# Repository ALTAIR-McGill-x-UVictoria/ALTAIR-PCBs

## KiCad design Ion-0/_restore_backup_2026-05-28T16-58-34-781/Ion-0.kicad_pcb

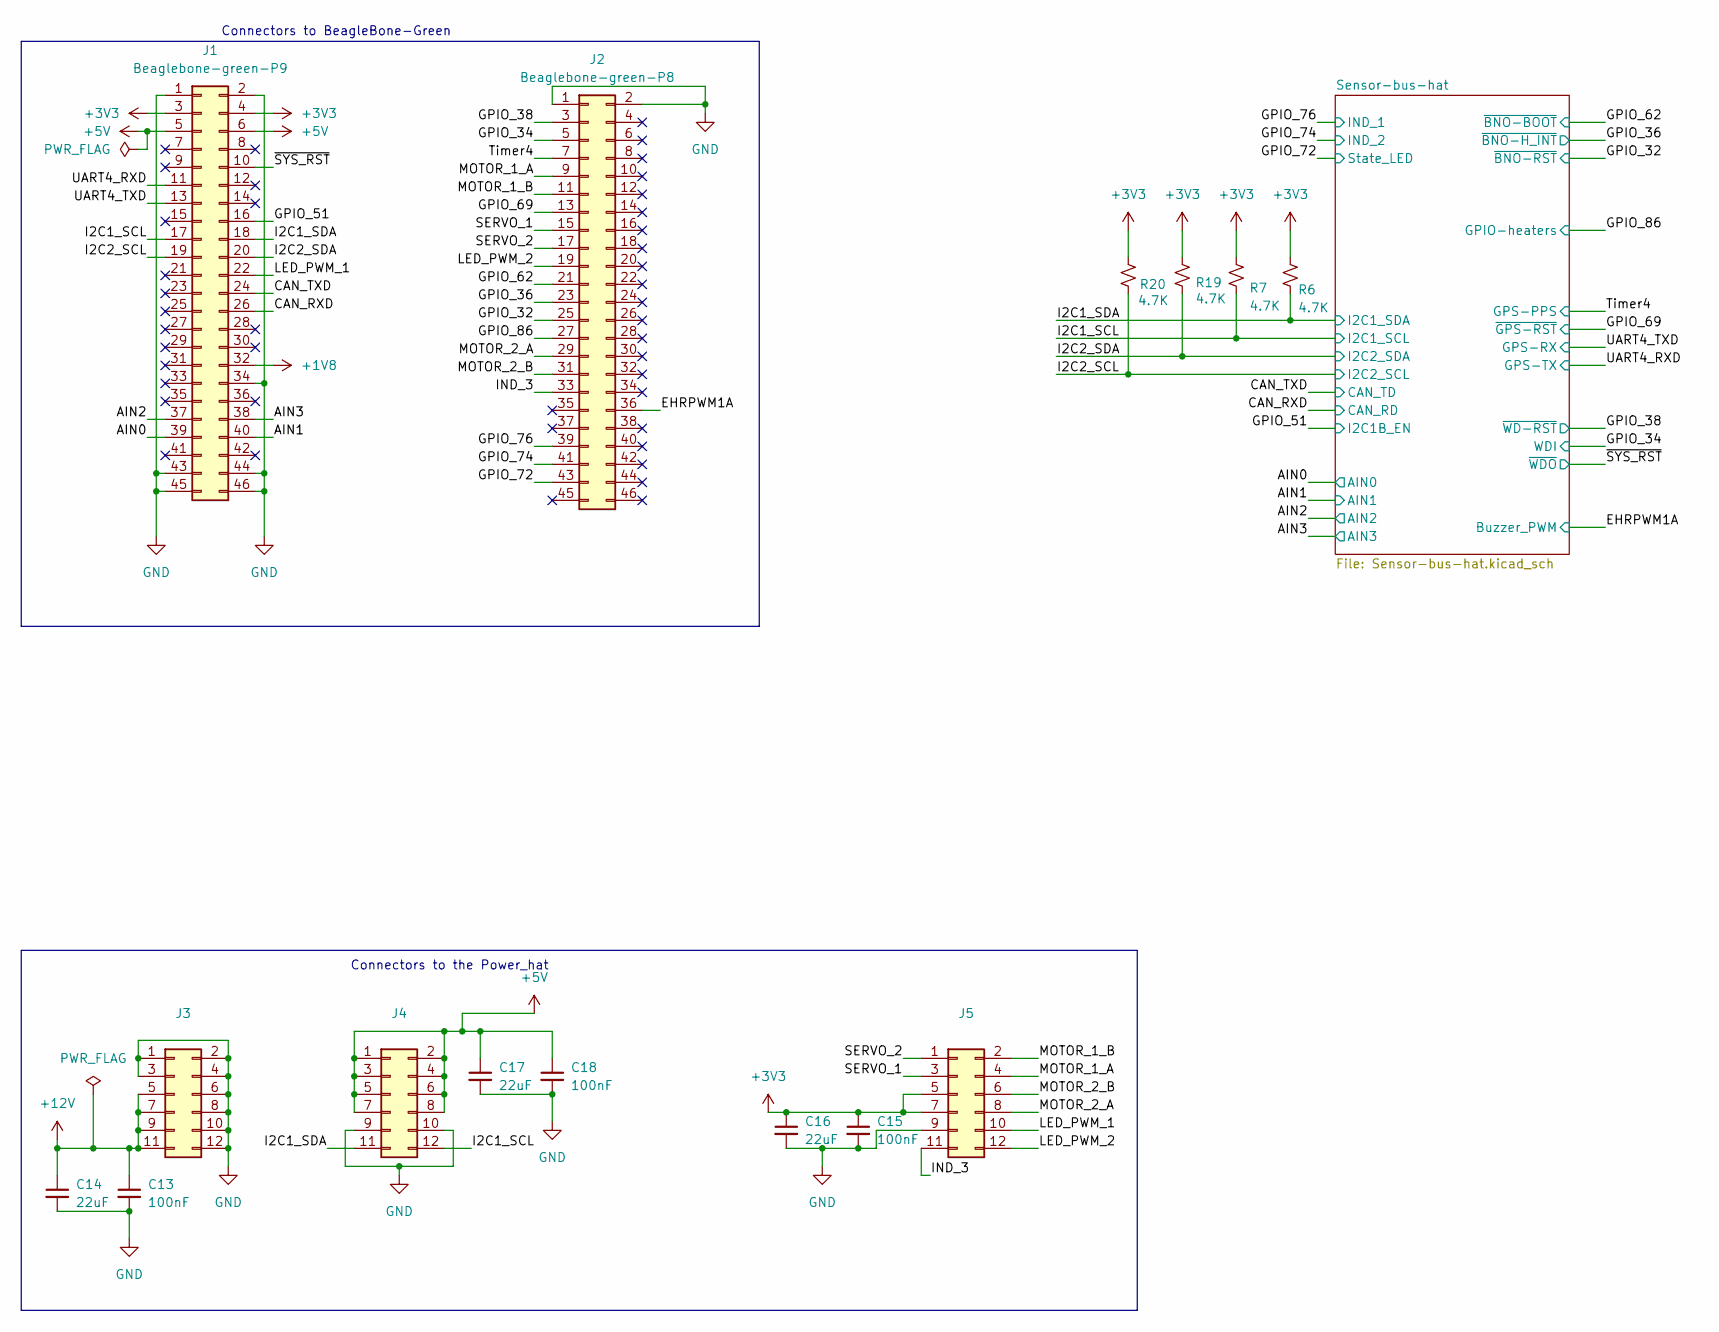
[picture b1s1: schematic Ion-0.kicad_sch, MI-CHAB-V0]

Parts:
C13, C15, C18: 100nF; C_0603_1608Metric
C14, C16, C17: 22uF; C_0603_1608Metric
J1: Beaglebone-green-P9; PinHeader_2x23_P2.54mm_Vertical
J2: Beaglebone-green-P8; PinHeader_2x23_P2.54mm_Vertical
J3, J4, J5: Conn_02x06_Odd_Even; PinSocket_2x06_P2.54mm_Vertical
R6, R7, R19, R20: 4.7K; R_0603_1608Metric_Pad0.98x0.95mm_HandSolder

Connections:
+1V8: J1.32; also elsewhere on the board
+3V3: C15.1, C16.1, J1.3, J1.4, J5.5, J5.7, R6.2, R7.1, R19.1, R20.1; also elsewhere on the board
+5V: C17.1, C18.1, J1.5, J1.6, J4.1, J4.2, J4.3, J4.4, J4.5, J4.6, J4.7, J4.8; also elsewhere on the board
+12V: C13.1, C14.1, J3.5, J3.7, J3.9, J3.11
/AIN0: J1.39; also elsewhere on the board
/AIN1: J1.40; also elsewhere on the board
/AIN2: J1.37; also elsewhere on the board
/AIN3: J1.38; also elsewhere on the board
/CAN_RXD: J1.26; also elsewhere on the board
/CAN_TXD: J1.24; also elsewhere on the board
/EHRPWM1A: J2.36; also elsewhere on the board
/GPIO_32: J2.25; also elsewhere on the board
/GPIO_34: J2.5; also elsewhere on the board
/GPIO_36: J2.23; also elsewhere on the board
/GPIO_38: J2.3; also elsewhere on the board
/GPIO_51: J1.16; also elsewhere on the board
/GPIO_62: J2.21; also elsewhere on the board
/GPIO_69: J2.13; also elsewhere on the board
/GPIO_72: J2.43; also elsewhere on the board
/GPIO_74: J2.41; also elsewhere on the board
/GPIO_76: J2.39; also elsewhere on the board
/GPIO_86: J2.27; also elsewhere on the board
/I2C1_SCL: J1.17, J4.12, R7.2; also elsewhere on the board
/I2C1_SDA: J1.18, J4.11, R6.1; also elsewhere on the board
/I2C2_SCL: J1.19, R20.2; also elsewhere on the board
/I2C2_SDA: J1.20, R19.2; also elsewhere on the board
/IND_3: J2.33, J5.11
/LED_PWM_1: J1.22, J5.10
/LED_PWM_2: J2.19, J5.12
/MOTOR_1_A: J2.9, J5.4
/MOTOR_1_B: J2.11, J5.2
/MOTOR_2_A: J2.29, J5.8
/MOTOR_2_B: J2.31, J5.6
/SERVO_1: J2.15, J5.3
/SERVO_2: J2.17, J5.1
/Timer4: J2.7; also elsewhere on the board
/UART4_RXD: J1.11; also elsewhere on the board
/UART4_TXD: J1.13; also elsewhere on the board
/~SYS_RST: J1.10; also elsewhere on the board
GND: C13.2, C14.2, C15.2, C16.2, C17.2, C18.2, J1.1, J1.2, J1.34, J1.43, J1.44, J1.45, J1.46, J2.1, J2.2, J3.1, J3.2, J3.3, J3.4, J3.6, J3.8, J3.10, J3.12, J4.9, J4.10, J5.9; also elsewhere on the board

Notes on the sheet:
Connectors to BeagleBone-Green
Connectors to the Power_hat

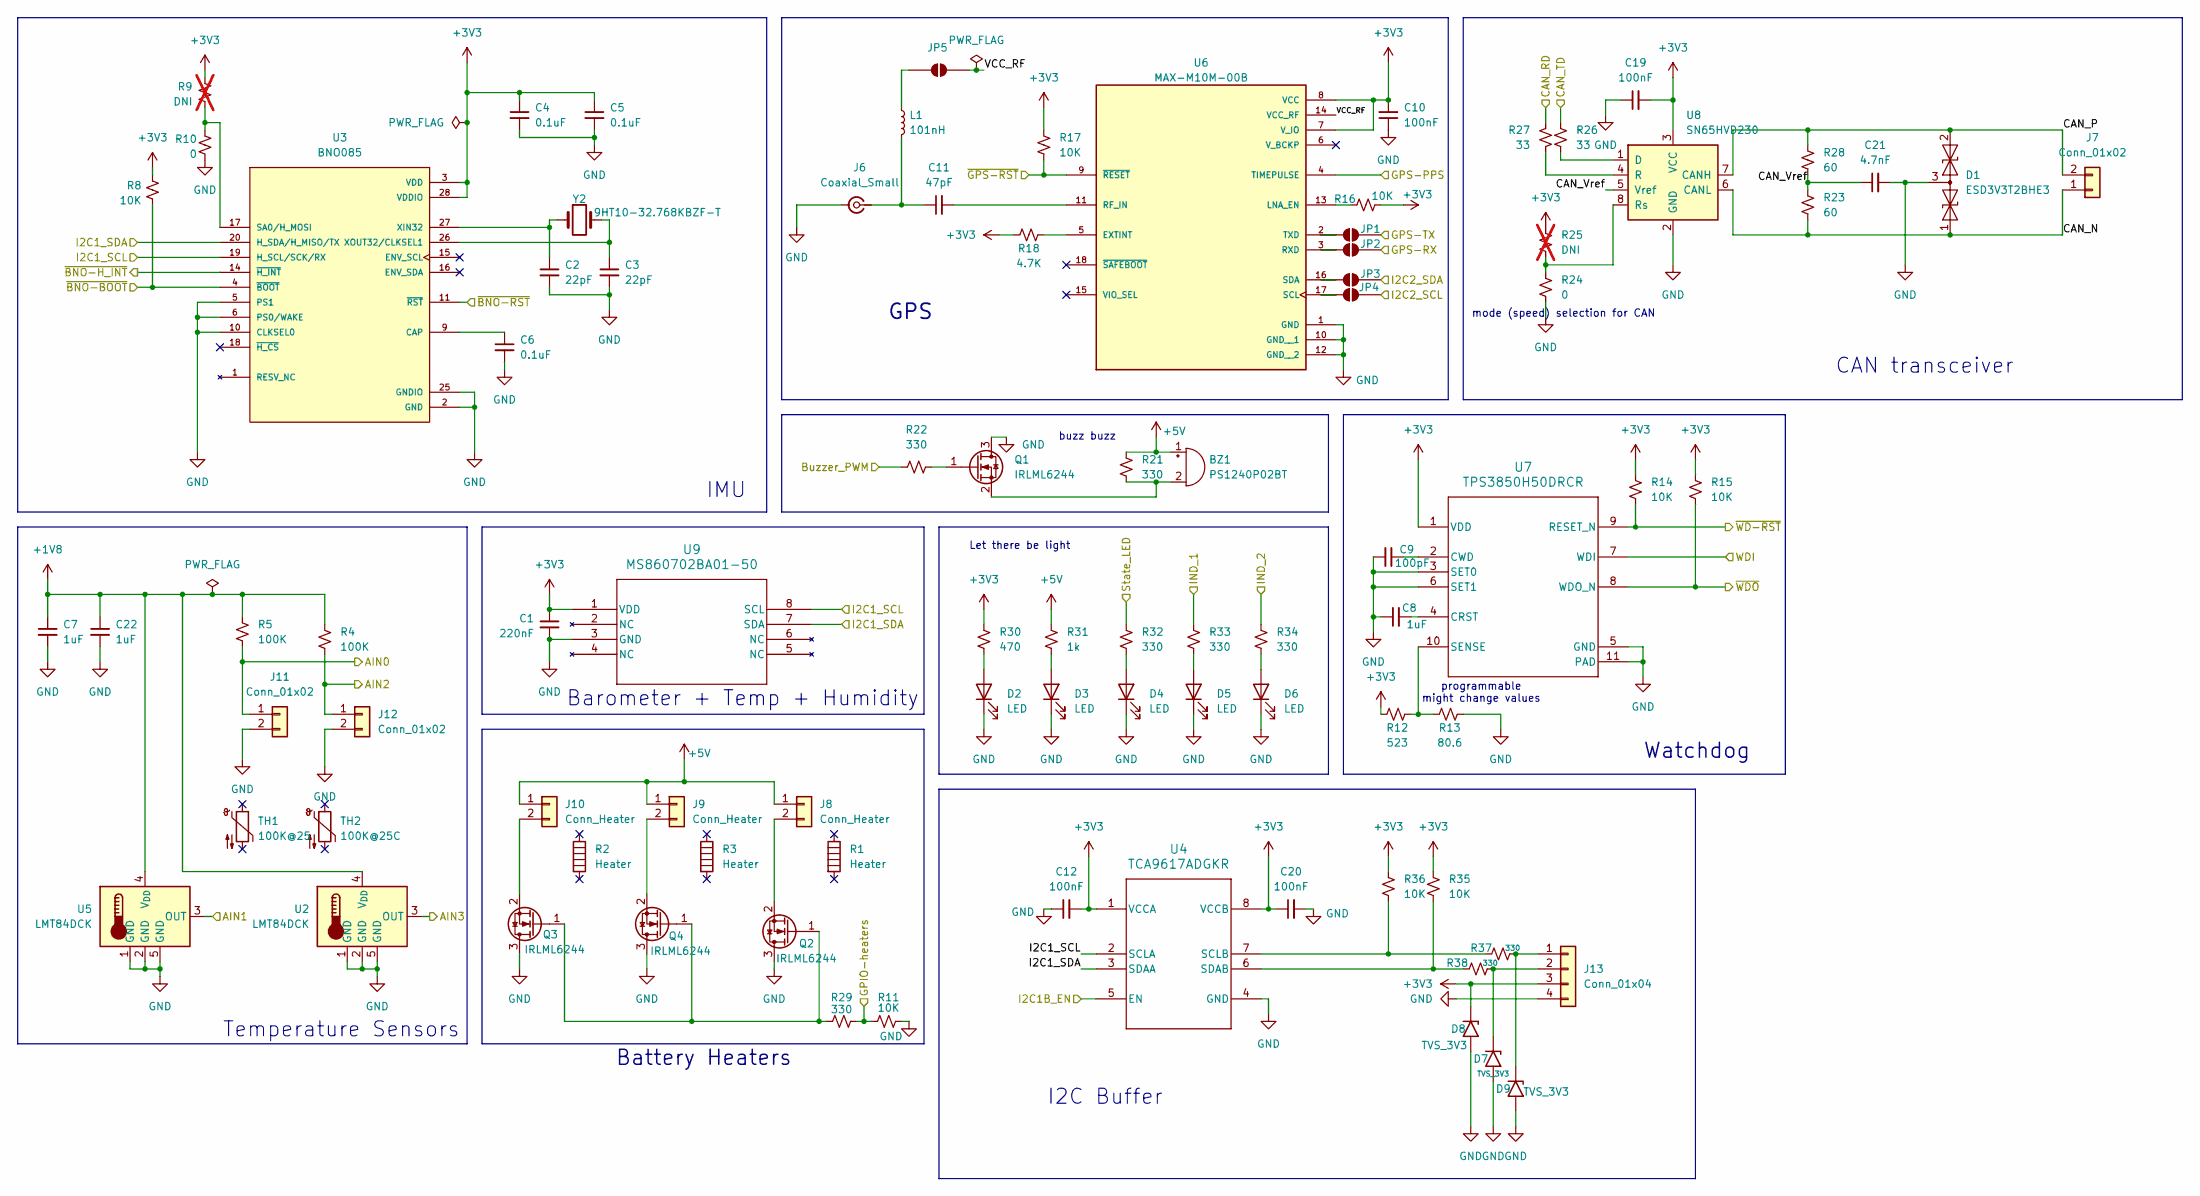
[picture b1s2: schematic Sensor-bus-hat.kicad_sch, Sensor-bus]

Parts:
BZ1: PS1240P02BT; Buzzer_TDK_PS1240P02BT_D12.2mm_H6.5mm
C1: 220nF; C_0603_1608Metric
C2, C3: 22pF; C_0603_1608Metric
C4, C5, C6: 0.1uF; C_0603_1608Metric
C7, C8, C22: 1uF; C_0603_1608Metric
C9: 100pF; C_0603_1608Metric
C10, C12, C19, C20: 100nF; C_0603_1608Metric
C11: 47pF; C_0603_1608Metric
C21: 4.7nF; C_0603_1608Metric
D1: ESD3V3T2BHE3; SOT-23
D2, D3, D4, D5, D6: LED; LED_0805_2012Metric
D7, D8, D9: TVS_3V3; D_0402_1005Metric_Pad0.77x0.64mm_HandSolder
J6: Coaxial_Small; SMA_Samtec_SMA-J-P-H-ST-EM1_EdgeMount
J7, J11, J12: Conn_01x02; JST_SH_SM02B-SRSS-TB_1x02-1MP_P1.00mm_Horizontal
J8, J9, J10: Conn_Heater; JST_SH_SM02B-SRSS-TB_1x02-1MP_P1.00mm_Horizontal
J13: Conn_01x04; JST_SH_SM04B-SRSS-TB_1x04-1MP_P1.00mm_Horizontal
JP1, JP2, JP3, JP4, JP5: SolderJumper_2_Open; SolderJumper-2_P1.3mm_Open_TrianglePad1.0x1.5mm
L1: 101nH; L_0402_1005Metric
Q1, Q2, Q3, Q4: IRLML6244; SOT-23
R1, R2, R3: Heater
R4, R5: 100K; R_0603_1608Metric_Pad0.98x0.95mm_HandSolder
R8, R11, R14, R15, R16, R17, R35, R36: 10K; R_0603_1608Metric_Pad0.98x0.95mm_HandSolder
R9, R25: DNI; R_0603_1608Metric_Pad0.98x0.95mm_HandSolder; not fitted
R10, R24: 0; R_0603_1608Metric_Pad0.98x0.95mm_HandSolder
R12: 523; R_0603_1608Metric_Pad0.98x0.95mm_HandSolder
R13: 80.6; R_0603_1608Metric_Pad0.98x0.95mm_HandSolder
R18: 4.7K; R_0603_1608Metric_Pad0.98x0.95mm_HandSolder
R21, R22, R29, R32, R33, R34, R37, R38: 330; R_0603_1608Metric_Pad0.98x0.95mm_HandSolder
R23, R28: 60; R_0603_1608Metric_Pad0.98x0.95mm_HandSolder
R26, R27: 33; R_0603_1608Metric_Pad0.98x0.95mm_HandSolder
R30: 470; R_0603_1608Metric_Pad0.98x0.95mm_HandSolder
R31: 1k; R_0603_1608Metric_Pad0.98x0.95mm_HandSolder
TH1: 100K@25
TH2: 100K@25C
U2, U5: LMT84DCK; SOT-353_SC-70-5
U3: BNO085; IC_BNO085; PARTREV v1.17
U4: TCA9617ADGKR; TCA9617A
U6: MAX-M10M-00B; XCVR_MAX-M10M-00B; PARTREV C1
U7: TPS3850H50DRCR; TPS3850
U8: SN65HVD230; SOIC-8_3.9x4.9mm_P1.27mm
U9: MS860702BA01-50; MS860702BA01-50_TEC
Y2: 9HT10-32.768KBZF-T; L_1206_3216Metric

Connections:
+1V8: C7.1, C22.1, R4.1, R5.1, U2.4 (V_{DD}), U5.4 (V_{DD}); also elsewhere on the board
+3V3: C1.1, C4.1, C5.1, C10.2, C12.2, C19.2, C20.1, D8.1 (A1), J13.3, R8.1, R9.1, R12.1, R14.1, R15.1, R16.2, R17.1, R18.2, R25.1, R30.1, R35.1, R36.1, U3.3 (VDD), U3.28 (VDDIO), U4.1 (VCCA), U4.8 (VCCB), U6.7 (V_IO), U6.8 (VCC), U7.1 (VDD), U8.3 (VCC), U9.1 (VDD); also elsewhere on the board
+5V: BZ1.1 (+), J8.1, J9.1, J10.1, R21.1, R31.1; also elsewhere on the board
/AIN0: J11.1, R5.2; also elsewhere on the board
/AIN1: U5.3 (OUT); also elsewhere on the board
/AIN2: J12.1, R4.2; also elsewhere on the board
/AIN3: U2.3 (OUT); also elsewhere on the board
/CAN_RXD: R27.1; also elsewhere on the board
/CAN_TXD: R26.1; also elsewhere on the board
/EHRPWM1A: R22.1; also elsewhere on the board
/GPIO_32: U3.11 (~RST); also elsewhere on the board
/GPIO_34: U7.7 (WDI); also elsewhere on the board
/GPIO_36: U3.14 (~H_INT); also elsewhere on the board
/GPIO_38: R14.2, U7.9 (RESET_N); also elsewhere on the board
/GPIO_51: U4.5 (EN); also elsewhere on the board
/GPIO_62: R8.2, U3.4 (~BOOT); also elsewhere on the board
/GPIO_69: R17.2, U6.9 (~RESET); also elsewhere on the board
/GPIO_72: R32.1; also elsewhere on the board
/GPIO_74: R34.1; also elsewhere on the board
/GPIO_76: R33.1; also elsewhere on the board
/GPIO_86: R11.1, R29.1; also elsewhere on the board
/I2C1_SCL: U3.19 (H_SCL/SCK/RX), U4.2 (SCLA), U9.8 (SCL); also elsewhere on the board
/I2C1_SDA: U3.20 (H_SDA/H_MISO/TX), U4.3 (SDAA), U9.7 (SDA); also elsewhere on the board
/I2C2_SCL: JP4.2 (B); also elsewhere on the board
/I2C2_SDA: JP3.2 (B); also elsewhere on the board
/Sensor-bus-hat/CAN_Vref: C21.1, R23.1, R28.2, U8.5 (Vref)
/Sensor-bus-hat/VCC_RF: JP5.2 (B), U6.14 (VCC_RF)
/Timer4: U6.4 (TIMEPULSE); also elsewhere on the board
/UART4_RXD: JP1.2 (B); also elsewhere on the board
/UART4_TXD: JP2.2 (B); also elsewhere on the board
/~SYS_RST: R15.2, U7.8 (WDO_N); also elsewhere on the board
GND: C1.2, C2.2, C3.2, C4.2, C5.2, C6.2, C7.2, C8.1, C9.2, C10.1, C12.1, C19.1, C20.2, C21.2, C22.2, D1.3 (common), D2.1 (K), D3.1 (K), D4.1 (K), D5.1 (K), D6.1 (K), D7.2 (A2), D8.2 (A2), D9.2 (A2), J6.2 (Ext), J11.2, J12.2, J13.4, Q1.3 (D), Q2.3 (D), Q3.3 (D), Q4.3 (D), R10.2, R11.2, R13.1, R24.2, U2.1 (GND), U2.2 (GND), U2.5 (GND), U3.2 (GND), U3.5 (PS1), U3.6 (PS0/WAKE), U3.10 (CLKSEL0), U3.25 (GNDIO), U4.4 (GND), U5.1 (GND), U5.2 (GND), U5.5 (GND), U6.1 (GND), U6.10 (GND__1), U6.12 (GND__2), U7.3 (SET0), U7.5 (GND), U7.6 (SET1), U7.11 (PAD), U8.2 (GND), U9.3 (GND); also elsewhere on the board
unnamed: BZ1.2 (-), Q1.2 (S), R21.2
unnamed: D2.2 (A), R30.2
unnamed: D3.2 (A), R31.2
unnamed: D4.2 (A), R32.2
unnamed: D5.2 (A), R33.2
unnamed: D6.2 (A), R34.2
unnamed: D7.1 (A1), J13.2, R38.2
unnamed: D9.1 (A1), J13.1, R37.2
unnamed: C11.1, J6.1 (In), L1.2
unnamed: J8.2, Q2.2 (S)
unnamed: J9.2, Q4.2 (S)
unnamed: J10.2, Q3.2 (S)
unnamed: JP1.1 (A), U6.2 (TXD)
unnamed: JP2.1 (A), U6.3 (RXD)
unnamed: JP3.1 (A), U6.16 (SDA)
unnamed: JP4.1 (A), U6.17 (SCL)
unnamed: JP5.1 (A), L1.1
unnamed: Q1.1 (G), R22.2
unnamed: Q2.1 (G), Q3.1 (G), Q4.1 (G), R29.2
unnamed: C6.1, U3.9 (CAP)
unnamed: R9.2, R10.1, U3.17 (SA0/H_MOSI)
unnamed: C2.1, U3.27 (XIN32), Y2.1
unnamed: C3.1, U3.26 (XOUT32/CLKSEL1), Y2.2
unnamed: R36.2, R37.1, U4.7 (SCLB)
unnamed: R35.2, R38.1, U4.6 (SDAB)
unnamed: R18.1, U6.5 (EXTINT)
unnamed: R16.1, U6.13 (LNA_EN)
unnamed: C11.2, U6.11 (RF_IN)
unnamed: C8.2, U7.4 (CRST)
unnamed: C9.1, U7.2 (CWD)
unnamed: R12.2, R13.2, U7.10 (SENSE)
unnamed: R26.2, U8.1 (D)
unnamed: R27.2, U8.4 (R)
unnamed: R24.1, R25.2, U8.8 (Rs)

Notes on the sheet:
Barometer + Temp + Humidity
Watchdog
IMU
Let there be light
buzz buzz
CAN transceiver
programmable might change values
GPS
I2C Buffer
mode (speed) selection for CAN
Battery Heaters
Temperature Sensors

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
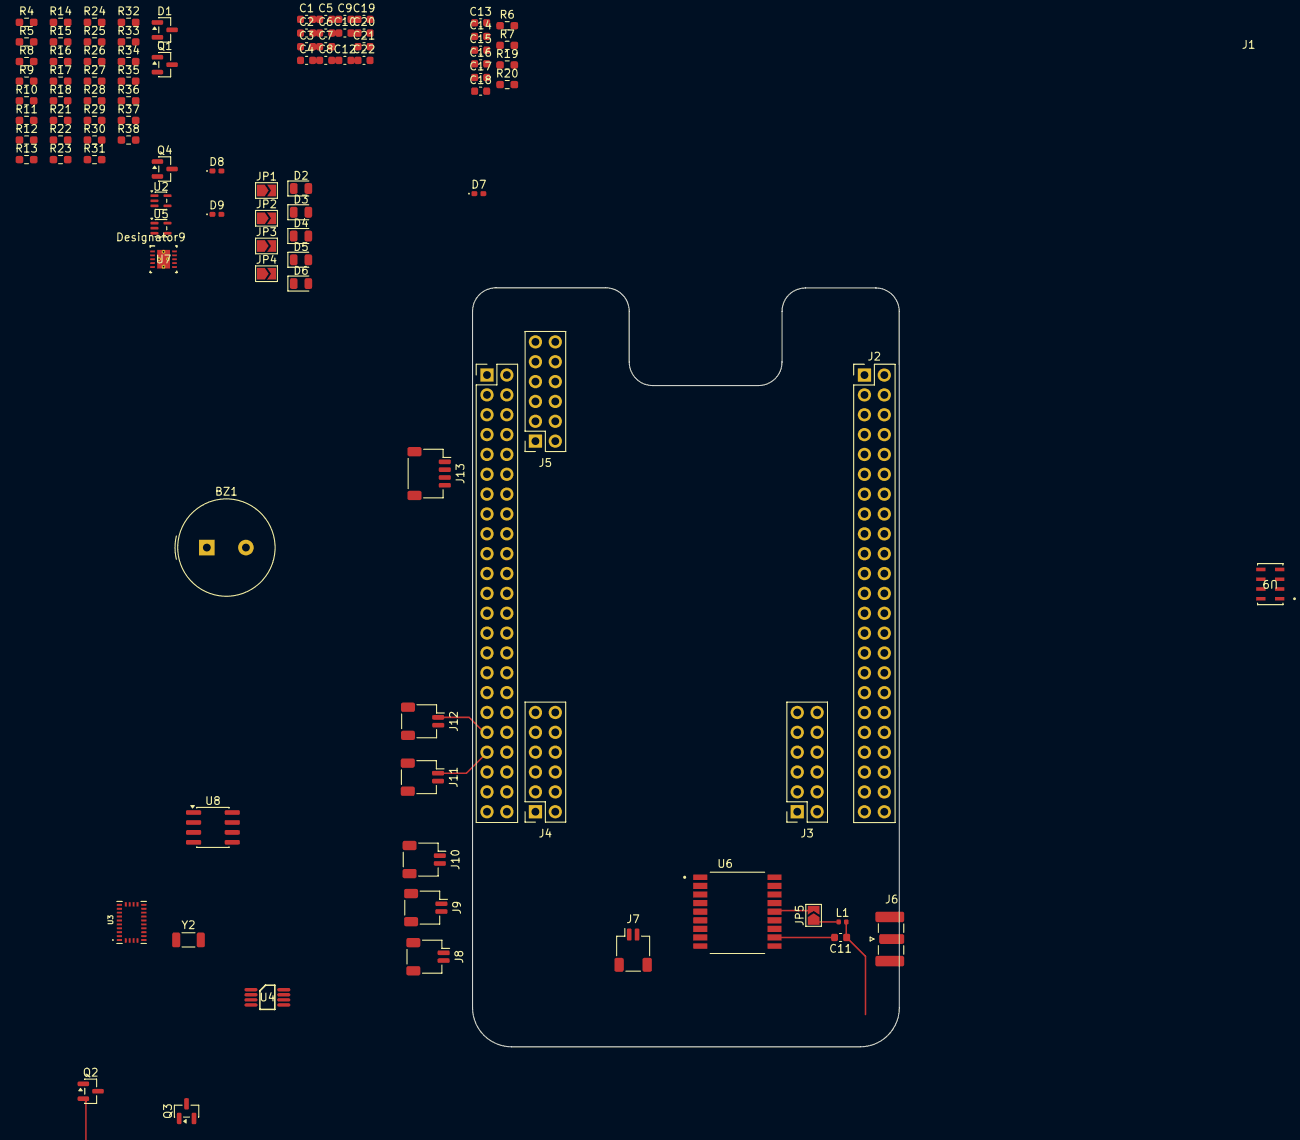
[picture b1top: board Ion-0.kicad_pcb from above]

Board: 4 copper layers, 54.6 x 97.1 mm, 99 parts (0 on the bottom side), 78 nets.
